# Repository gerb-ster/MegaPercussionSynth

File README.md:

# Mega Percussion Synth

A eurorack adaptation of Thomas Henry's MegaPercussionSynth

## Status: Work in Progress

- done: first schematic & board design
- todo: breadboard and test
- todo: design frontpanel
- todo: order PCB and build prototype

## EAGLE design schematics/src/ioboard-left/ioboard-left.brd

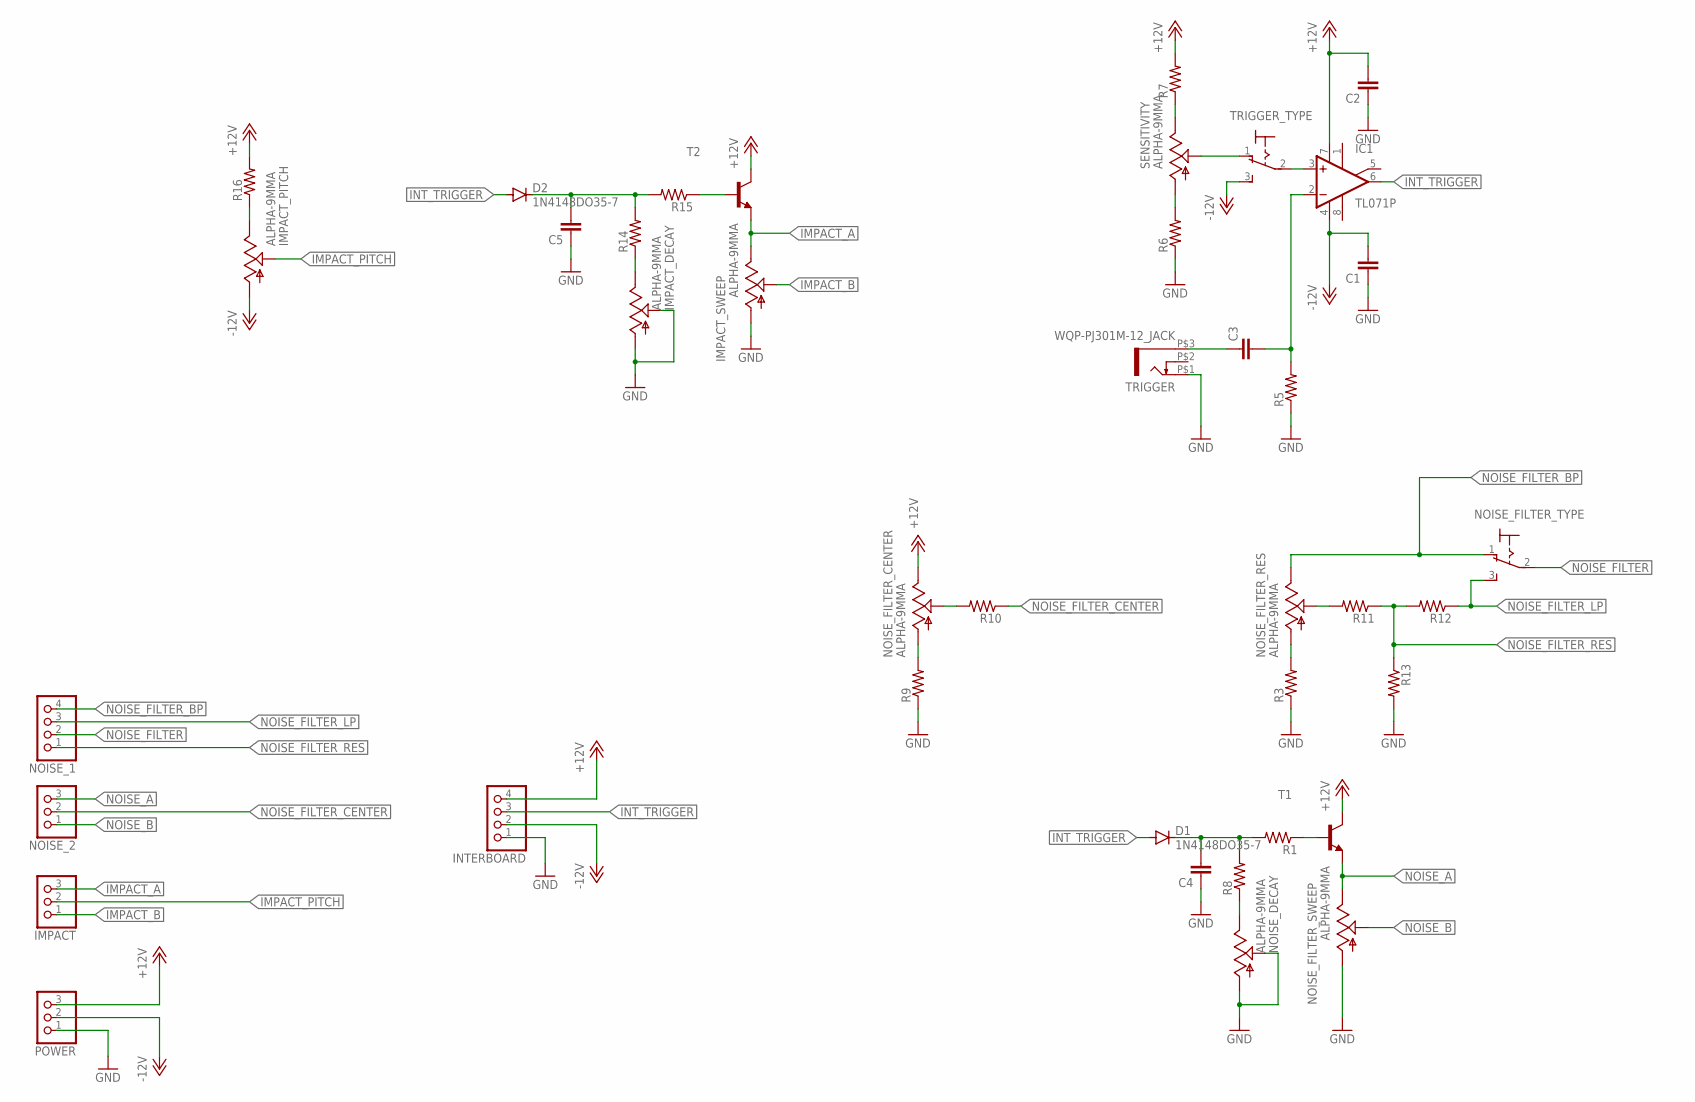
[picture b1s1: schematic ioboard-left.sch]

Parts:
C1, C2, C3, C4, C5: C-EU050-024X044; C050-024X044
D1, D2: 1N4148DO35-7; DO35-7
IC1: TL071P; DIL08
IMPACT: PINHD-1X3; 1X03
IMPACT_DECAY: ALPHA-9MMA; EVUF
IMPACT_PITCH: ALPHA-9MMA; EVUF
IMPACT_SWEEP: ALPHA-9MMA; EVUF
INTERBOARD: PINHD-1X4; 1X04
NOISE_1: PINHD-1X4; 1X04
NOISE_2: PINHD-1X3; 1X03
NOISE_DECAY: ALPHA-9MMA; EVUF
NOISE_FILTER_CENTER: ALPHA-9MMA; EVUF
NOISE_FILTER_RES: ALPHA-9MMA; EVUF
NOISE_FILTER_SWEEP: ALPHA-9MMA; EVUF
NOISE_FILTER_TYPE: M9040P
POWER: PINHD-1X3; 1X03
R1, R3, R5, R6, R7, R8, R9, R10, R11, R12, R13, R14, R15, R16: R-US_0207/7; 0207/7
SENSITIVITY: ALPHA-9MMA; EVUF
T1, T2: 2N3904-NPN-TO92-EBC; TO92-EBC
TRIGGER: WQP-PJ301M-12_JACK
TRIGGER_TYPE: M9040P

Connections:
+12V: C2.2, IC1.7 (V+), INTERBOARD.4, NOISE_FILTER_CENTER.3 (E), POWER.3, R7.2, R16.2, T1.C, T2.C
-12V: C1.2, IC1.4 (V-), IMPACT_PITCH.1 (A), INTERBOARD.2, POWER.2, TRIGGER_TYPE.3 (S)
GND: C1.1, C2.1, C4.1, C5.1, IMPACT_DECAY.1 (A), IMPACT_DECAY.2 (S), IMPACT_SWEEP.1 (A), INTERBOARD.1, NOISE_DECAY.1 (A), NOISE_DECAY.2 (S), NOISE_FILTER_SWEEP.1 (A), POWER.1, R3.1, R5.1, R6.1, R9.1, R13.2, TRIGGER.P$1 (2)
IMPACT_A: IMPACT.3, IMPACT_SWEEP.3 (E), T2.E
IMPACT_B: IMPACT.1, IMPACT_SWEEP.2 (S)
IMPACT_PITCH: IMPACT.2, IMPACT_PITCH.2 (S)
INT_TRIGGER: D1.A, D2.A, IC1.6 (OUT), INTERBOARD.3
unnamed: R7.1, SENSITIVITY.3 (E)
unnamed: R6.2, SENSITIVITY.1 (A)
unnamed: SENSITIVITY.2 (S), TRIGGER_TYPE.1 (O)
unnamed: IC1.3 (+IN), TRIGGER_TYPE.2
unnamed: C3.1, TRIGGER.P$3 (1)
unnamed: C3.2, IC1.2 (-IN), R5.2
unnamed: C4.2, D1.C, R1.2, R8.2
unnamed: NOISE_DECAY.3 (E), R8.1
unnamed: R1.1, T1.B
unnamed: NOISE_FILTER_CENTER.1 (A), R9.2
unnamed: NOISE_FILTER_CENTER.2 (S), R10.2
unnamed: NOISE_FILTER_RES.1 (A), R3.2
unnamed: NOISE_FILTER_RES.2 (S), R11.2
unnamed: C5.2, D2.C, R14.2, R15.2
unnamed: IMPACT_DECAY.3 (E), R14.1
unnamed: R15.1, T2.B
unnamed: IMPACT_PITCH.3 (E), R16.1
NOISE_A: NOISE_2.3, NOISE_FILTER_SWEEP.3 (E), T1.E
NOISE_B: NOISE_2.1, NOISE_FILTER_SWEEP.2 (S)
NOISE_FILTER: NOISE_1.2, NOISE_FILTER_TYPE.2
NOISE_FILTER_BP: NOISE_1.4, NOISE_FILTER_RES.3 (E), NOISE_FILTER_TYPE.1 (O)
NOISE_FILTER_CENTER: NOISE_2.2, R10.1
NOISE_FILTER_LP: NOISE_1.3, NOISE_FILTER_TYPE.3 (S), R12.1
NOISE_FILTER_RES: NOISE_1.1, R11.1, R12.2, R13.1

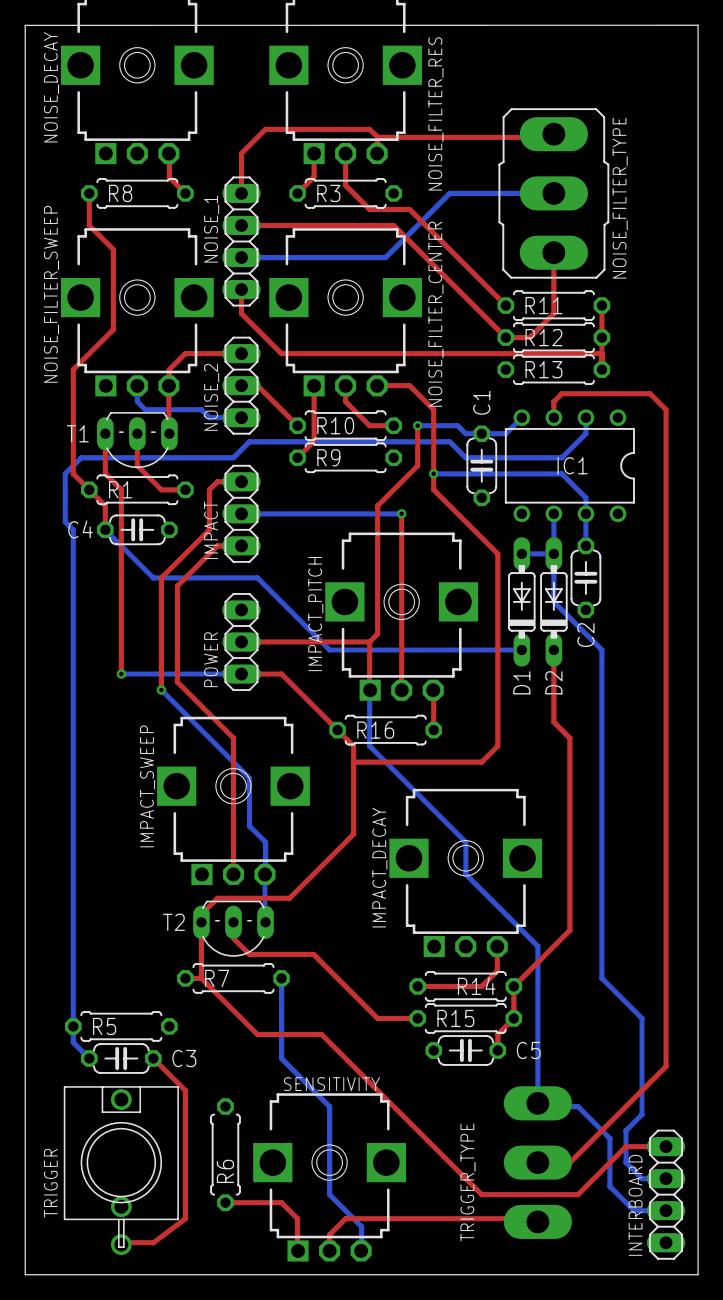
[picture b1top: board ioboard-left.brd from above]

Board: 2 copper layers, 53.3 x 99.1 mm, 40 parts (1 on the bottom side), 31 nets.

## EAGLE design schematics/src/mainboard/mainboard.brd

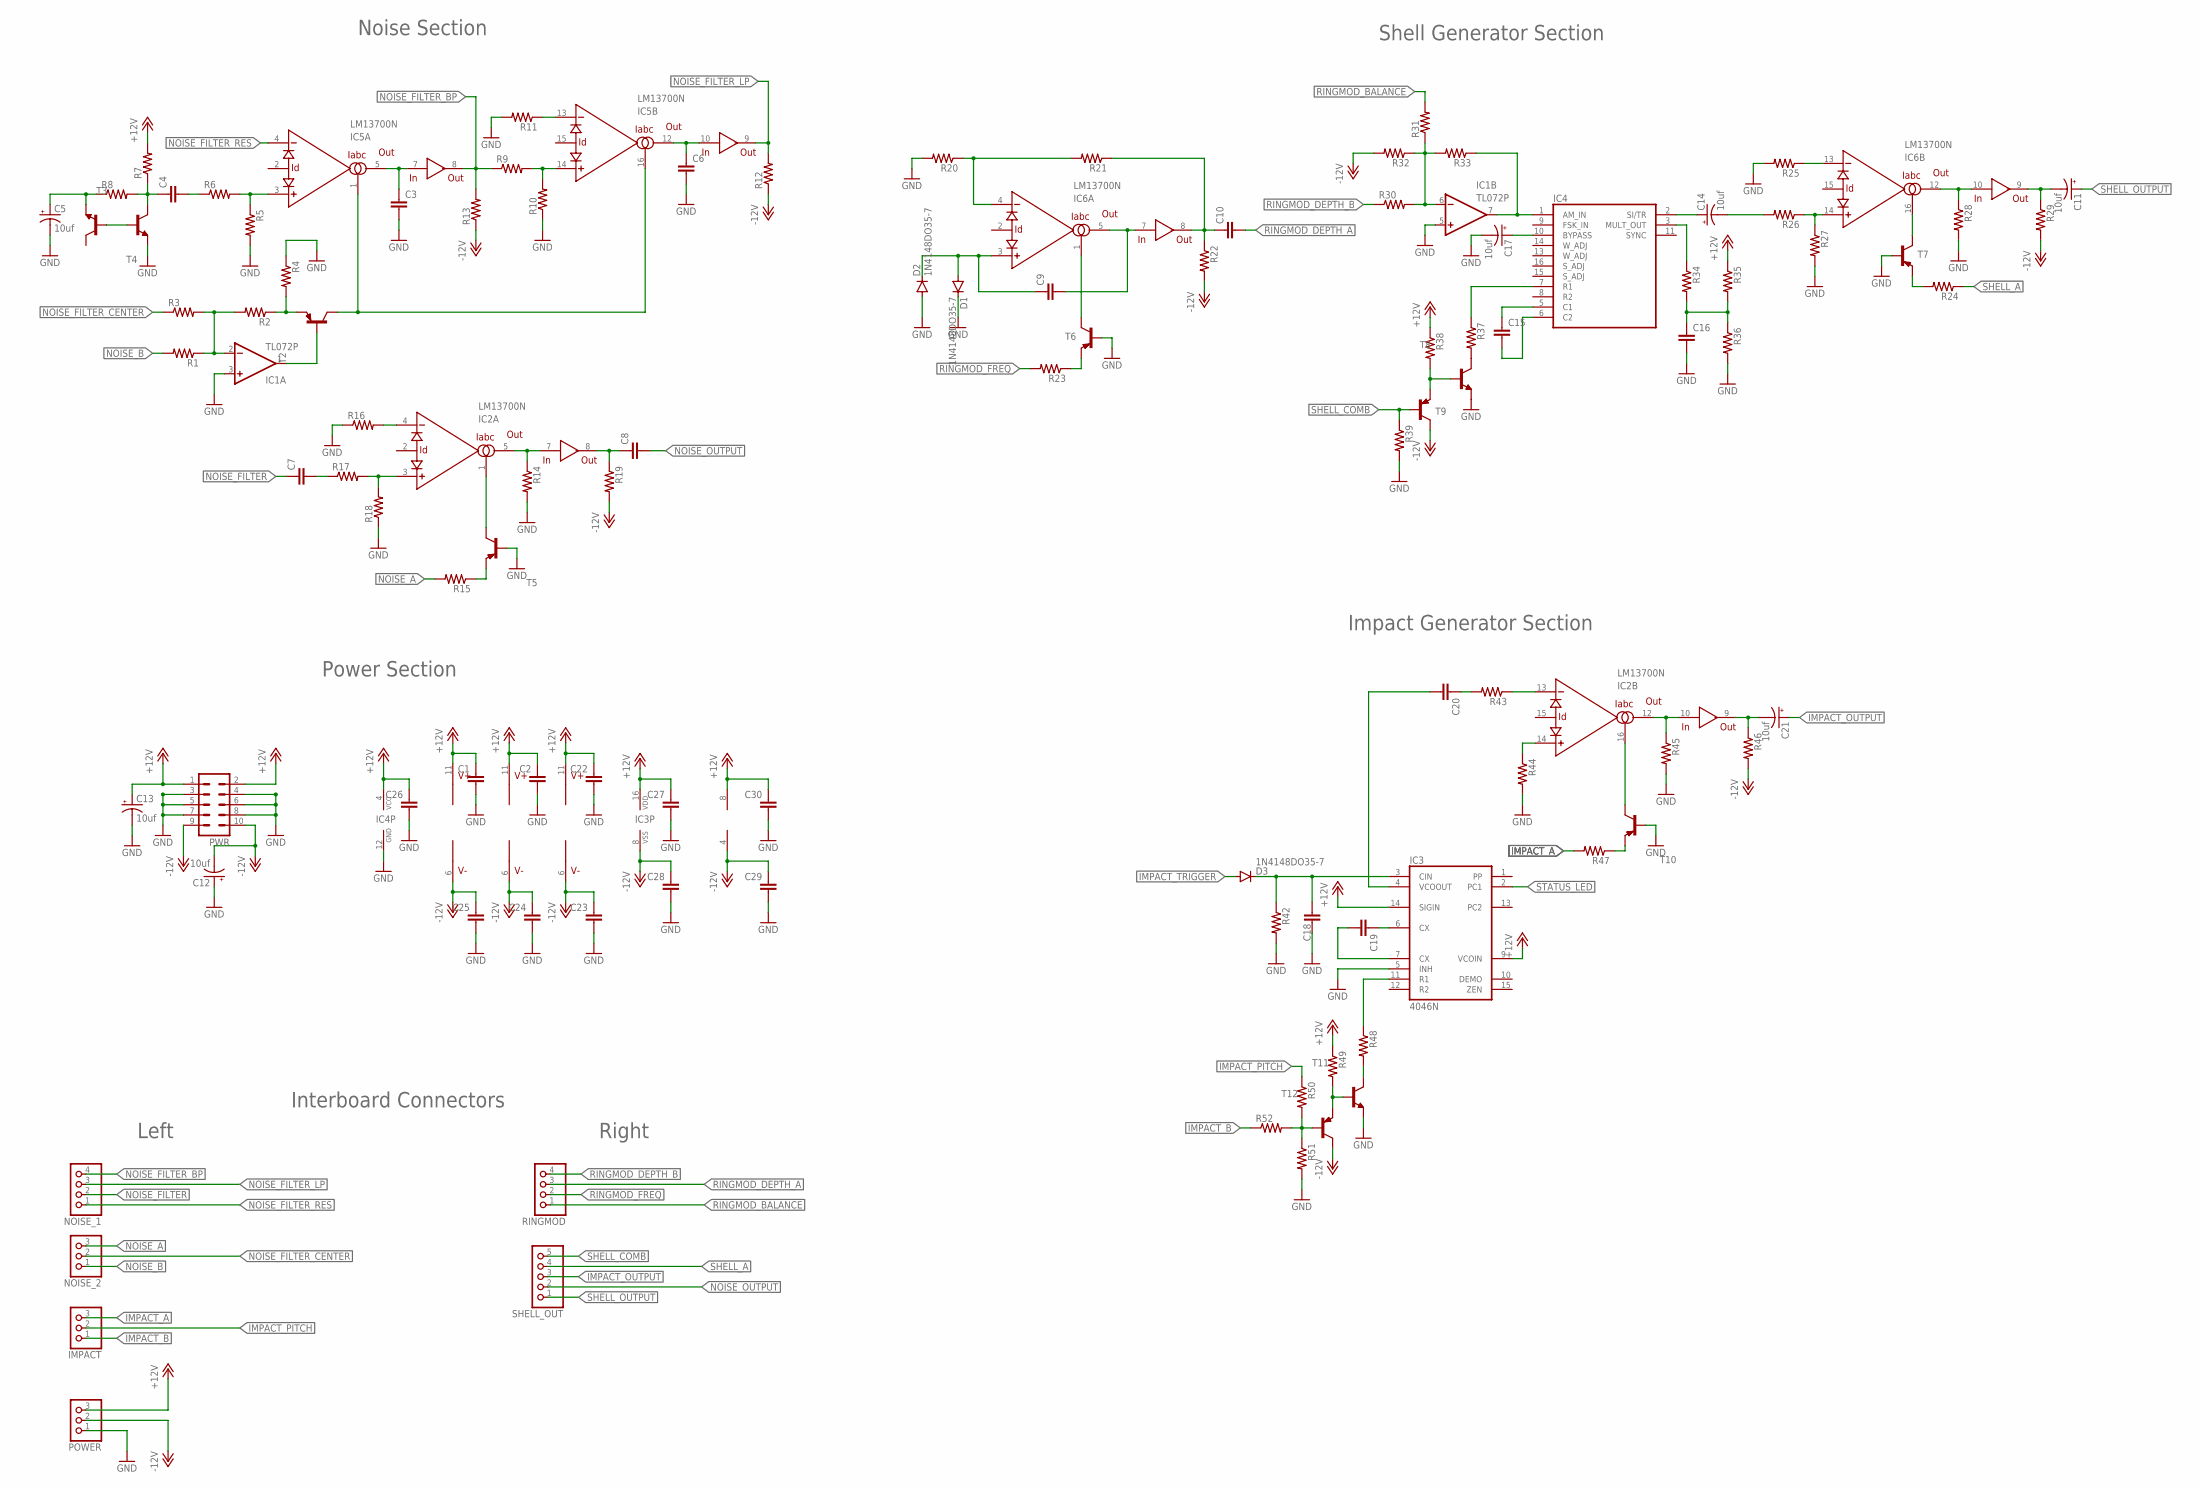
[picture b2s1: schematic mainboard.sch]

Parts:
C1, C2, C3, C4, C6, C7, C8, C9, C10, C15, C16, C18, C19, C20, C22, C23, C24, C25, C26, C27, C28, C29, C30: C-EU050-024X044; C050-024X044
C5, C11, C12, C13, C14, C17, C21: 10uf; E2,5-5
D1, D2, D3: 1N4148DO35-7; DO35-7
IC1: TL072P; DIL08
IC2, IC5, IC6: LM13700N; DIL16
IC3: 4046N; DIL16
IC4: XR-2206; DIL16
IMPACT: PINHD-1X3; 1X03
NOISE_1: PINHD-1X4; 1X04
NOISE_2: PINHD-1X3; 1X03
POWER: PINHD-1X3; 1X03
PWR: ML10
R1, R2, R3, R4, R5, R6, R7, R8, R9, R10, R11, R12, R13, R14, R15, R16, R17, R18, R19, R20, R21, R22, R23, R24, R25, R26, R27, R28, R29, R30, R31, R32, R33, R34, R35, R36, R37, R38, R39, R42, R43, R44, R45, R46, R47, R48, R49, R50, R51, R52: R-US_0207/7; 0207/7
RINGMOD: PINHD-1X4; 1X04
SHELL_OUT: PINHD-1X5; 1X05
T2, T5, T6, T7, T9, T10, T12: 2N3906-PNP-TO92-EBC; TO92-EBC
T3, T4, T8, T11: 2N3904-NPN-TO92-EBC; TO92-EBC

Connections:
+12V: C1.1, C2.1, C13.+, C22.1, C26.1, C27.1, C30.1, IC1.8 (V+), IC2.11 (V+), IC3.9 (VCOIN), IC3.14 (SIGIN), IC3.16 (VDD), IC4.4 (VCC), IC5.11 (V+), IC6.11 (V+), POWER.3, PWR.1, PWR.2, R7.2, R35.1, R38.1, R49.1
-12V: C12.-, C23.1, C24.1, C25.1, C28.1, C29.1, IC1.4 (V-), IC2.6 (V-), IC3.8 (VSS), IC5.6 (V-), IC6.6 (V-), POWER.2, PWR.9, PWR.10, R12.1, R13.1, R19.2, R22.2, R29.2, R32.2, R46.2, T9.C, T12.C
GND: C1.2, C2.2, C3.2, C5.-, C6.2, C12.+, C13.-, C16.2, C17.-, C18.1, C22.2, C23.2, C24.2, C25.2, C26.2, C27.2, C28.2, C29.2, C30.2, D1.C, D2.A, IC1.3 (+IN), IC1.5 (+IN), IC3.5 (INH), IC4.12 (GND), POWER.1, PWR.3, PWR.4, PWR.5, PWR.6, PWR.7, PWR.8, R4.1, R5.2, R10.1, R11.2, R14.2, R16.1, R18.1, R20.2, R25.2, R27.2, R28.2, R36.2, R39.2, R42.2, R44.2, R45.2, R51.2, T3.E, T5.B, T6.B, T7.B, T8.E, T10.B, T11.E
IMPACT_A: IMPACT.3, R47.2
IMPACT_B: IMPACT.1, R52.1
IMPACT_OUTPUT: C21.+, SHELL_OUT.3
IMPACT_PITCH: IMPACT.2, R50.1
IMPACT_TRIGGER: D3.A
unnamed: IC1.2 (-IN), R1.1, R2.2, R3.2
unnamed: IC5.1 (IABC), IC5.16 (IABC), T2.C
unnamed: IC1.1 (OUT), T2.B
unnamed: R2.1, R4.2, T2.E
unnamed: C3.1, IC5.5 (OUT), IC5.7 (IN)
unnamed: C5.+, R8.1, T4.E
unnamed: C4.1, R7.1, R8.2, T3.C
unnamed: T3.B, T4.B
unnamed: C4.2, R6.1
unnamed: IC5.3 (+IN), R5.1, R6.2
unnamed: C6.1, IC5.10 (IN), IC5.12 (OUT)
unnamed: IC5.14 (+IN), R9.2, R10.2
unnamed: IC5.13 (-IN), R11.1
unnamed: IC2.4 (-IN), R16.2
unnamed: IC2.3 (+IN), R17.2, R18.2
unnamed: C7.2, R17.1
unnamed: IC2.1 (IABC), T5.C
unnamed: C9.1, D1.A, D2.C, IC6.3 (+IN)
unnamed: R15.1, T5.E
unnamed: IC2.5 (OUT), IC2.7 (IN), R14.1
unnamed: C8.1, IC2.8 (OUT), R19.1
unnamed: C9.2, IC6.5 (OUT), IC6.7 (IN)
unnamed: C10.1, IC6.8 (OUT), R21.1, R22.1
unnamed: IC6.1 (IABC), T6.C
unnamed: R23.1, T6.E
unnamed: IC6.4 (-IN), R20.1, R21.2
unnamed: IC1.6 (-IN), R30.2, R31.1, R32.1, R33.2
unnamed: IC1.7 (OUT), IC4.1 (AM_IN), R33.1
unnamed: C14.+, IC4.2 (SI/TR)
unnamed: C14.-, R26.2
unnamed: IC6.14 (+IN), R26.1, R27.1
unnamed: IC6.13 (-IN), R25.1
unnamed: IC6.16 (IABC), T7.C
unnamed: IC6.10 (IN), IC6.12 (OUT), R28.1
unnamed: R24.2, T7.E
unnamed: C11.-, IC6.9 (OUT), R29.1
unnamed: C15.2, IC4.6 (C2)
unnamed: C15.1, IC4.5 (C1)
unnamed: IC4.3 (MULT_OUT), R34.1
unnamed: C17.+, IC4.10 (BYPASS)
unnamed: C16.1, R34.2, R35.2, R36.1
unnamed: IC4.7 (R1), R37.1
unnamed: R37.2, T8.C
unnamed: R38.2, T8.B, T9.E
unnamed: C20.1, R43.2
unnamed: IC2.13 (-IN), R43.1
unnamed: IC2.14 (+IN), R44.1
unnamed: IC2.10 (IN), IC2.12 (OUT), R45.1
unnamed: IC2.16 (IABC), T10.C
unnamed: R50.2, R51.1, R52.2, T12.B
unnamed: R47.1, T10.E
unnamed: C21.-, IC2.9 (OUT), R46.1
unnamed: C20.2, IC3.4 (VCOOUT)
unnamed: C19.1, IC3.6 (CX)
unnamed: C19.2, IC3.7 (CX)
unnamed: R49.2, T11.B, T12.E
unnamed: C18.2, D3.C, IC3.3 (CIN), R42.1
unnamed: R48.2, T11.C
unnamed: IC3.11 (R1), R48.1
NOISE_A: NOISE_2.3, R15.2
NOISE_B: NOISE_2.1, R1.2
NOISE_FILTER: C7.1, NOISE_1.2
NOISE_FILTER_BP: IC5.8 (OUT), NOISE_1.4, R9.1, R13.2
NOISE_FILTER_CENTER: NOISE_2.2, R3.1
NOISE_FILTER_LP: IC5.9 (OUT), NOISE_1.3, R12.2
NOISE_FILTER_RES: IC5.4 (-IN), NOISE_1.1
NOISE_OUTPUT: C8.2, SHELL_OUT.2
RINGMOD_BALANCE: R31.2, RINGMOD.1
RINGMOD_DEPTH_A: C10.2, RINGMOD.3
RINGMOD_DEPTH_B: R30.1, RINGMOD.4
RINGMOD_FREQ: R23.2, RINGMOD.2
SHELL_A: R24.1, SHELL_OUT.4
SHELL_COMB: R39.1, SHELL_OUT.5, T9.B
SHELL_OUTPUT: C11.+, SHELL_OUT.1
STATUS_LED: IC3.2 (PC1)

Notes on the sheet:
Noise Section
Shell Generator Section
Impact Generator Section
Power Section
Interboard Connectors
Left
Right

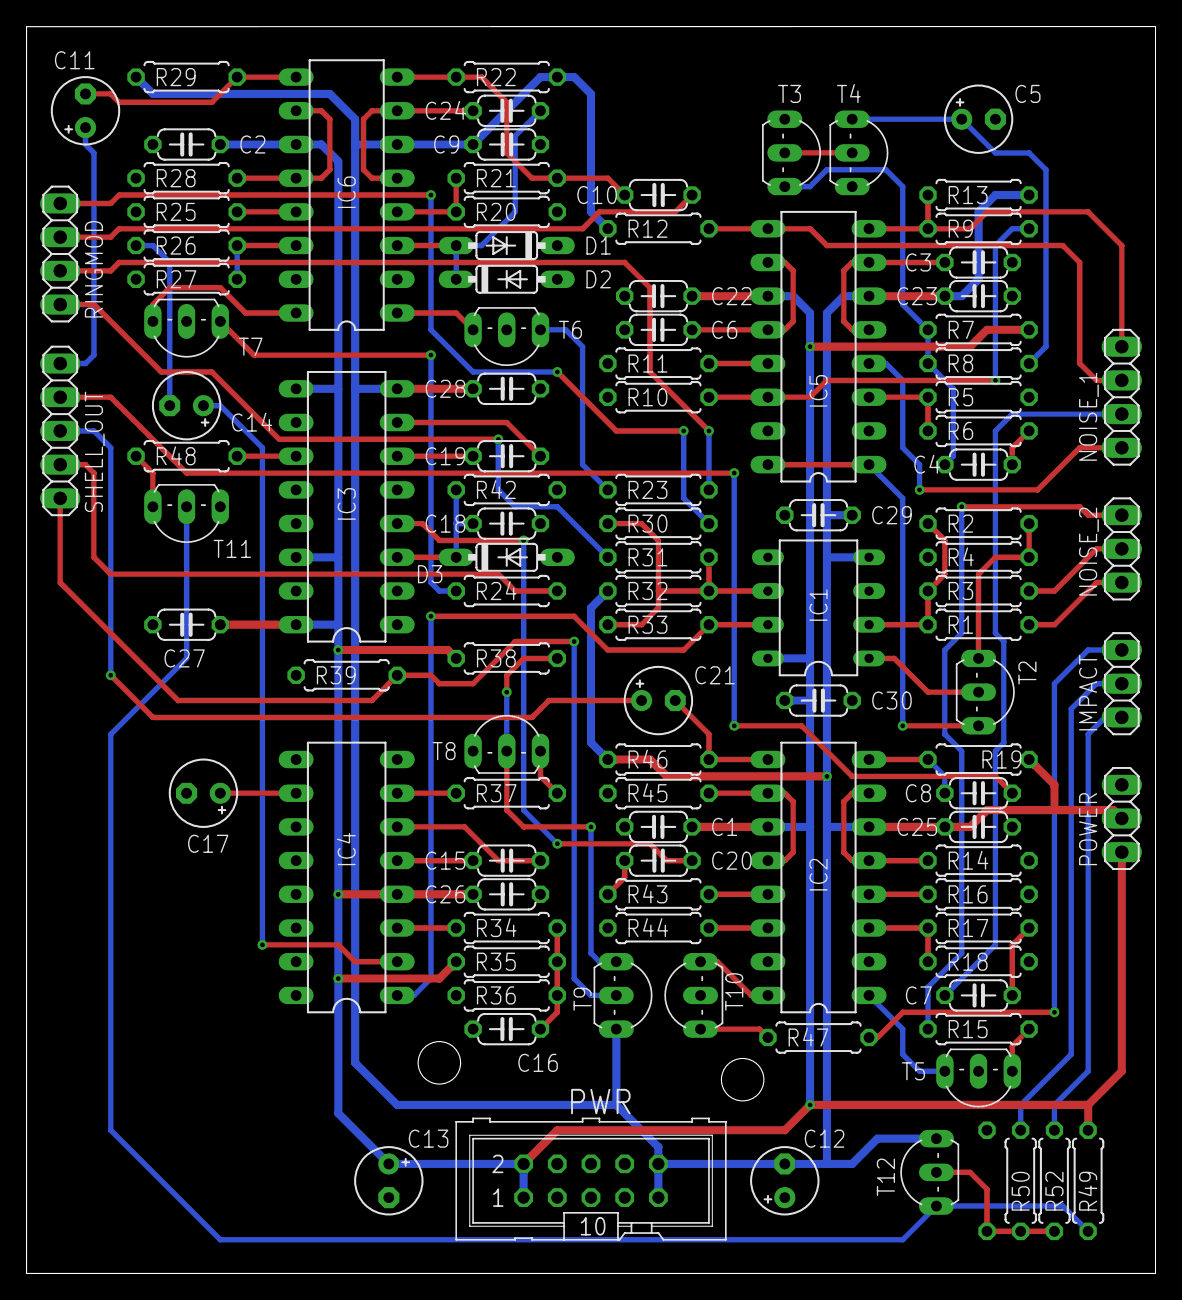
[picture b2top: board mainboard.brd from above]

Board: 2 copper layers, 85.1 x 94.0 mm, 107 parts (1 on the bottom side), 81 nets.

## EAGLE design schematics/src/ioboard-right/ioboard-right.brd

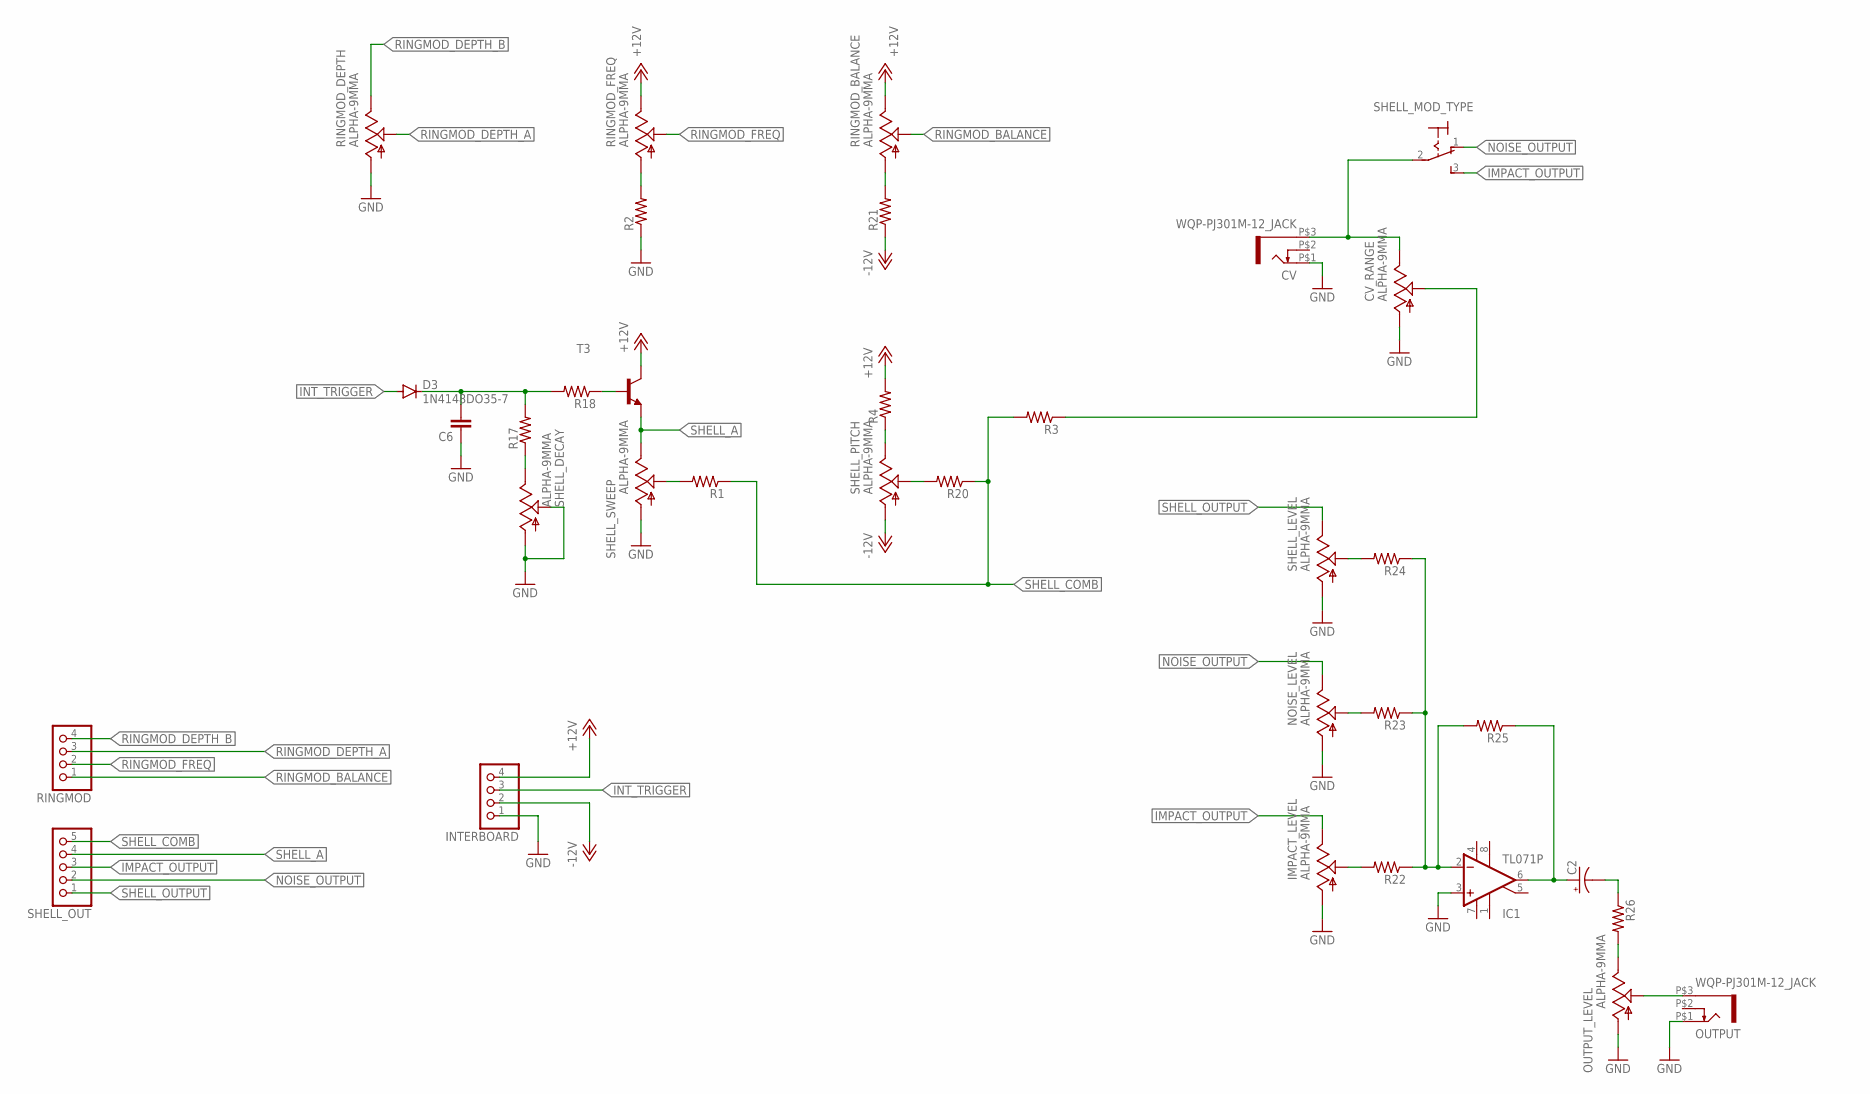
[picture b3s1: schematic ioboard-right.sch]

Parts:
C2: CPOL-USE2.5-6; E2,5-6
C6: C-EU050-024X044; C050-024X044
CV: WQP-PJ301M-12_JACK
CV_RANGE: ALPHA-9MMA; EVUF
D3: 1N4148DO35-7; DO35-7
IC1: TL071P; DIL08
IMPACT_LEVEL: ALPHA-9MMA; EVUF
INTERBOARD: PINHD-1X4; 1X04
NOISE_LEVEL: ALPHA-9MMA; EVUF
OUTPUT: WQP-PJ301M-12_JACK
OUTPUT_LEVEL: ALPHA-9MMA; EVUF
R1, R2, R3, R4, R17, R18, R20, R21, R22, R23, R24, R25, R26: R-US_0207/7; 0207/7
RINGMOD: PINHD-1X4; 1X04
RINGMOD_BALANCE: ALPHA-9MMA; EVUF
RINGMOD_DEPTH: ALPHA-9MMA; EVUF
RINGMOD_FREQ: ALPHA-9MMA; EVUF
SHELL_DECAY: ALPHA-9MMA; EVUF
SHELL_LEVEL: ALPHA-9MMA; EVUF
SHELL_MOD_TYPE: M9040P
SHELL_OUT: PINHD-1X5; 1X05
SHELL_PITCH: ALPHA-9MMA; EVUF
SHELL_SWEEP: ALPHA-9MMA; EVUF
T3: 2N3904-NPN-TO92-EBC; TO92-EBC

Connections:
+12V: INTERBOARD.4, R4.2, RINGMOD_BALANCE.3 (E), RINGMOD_FREQ.3 (E), T3.C
-12V: INTERBOARD.2, R21.1, SHELL_PITCH.1 (A)
GND: C6.1, CV.P$1 (2), CV_RANGE.1 (A), IC1.3 (+IN), IMPACT_LEVEL.1 (A), INTERBOARD.1, NOISE_LEVEL.1 (A), OUTPUT.P$1 (2), OUTPUT_LEVEL.1 (A), R2.1, RINGMOD_DEPTH.1 (A), SHELL_DECAY.1 (A), SHELL_DECAY.2 (S), SHELL_LEVEL.1 (A), SHELL_SWEEP.1 (A)
IMPACT_OUTPUT: IMPACT_LEVEL.3 (E), SHELL_MOD_TYPE.3 (S), SHELL_OUT.3
INT_TRIGGER: D3.A, INTERBOARD.3
unnamed: R1.2, SHELL_SWEEP.2 (S)
unnamed: CV_RANGE.2 (S), R3.1
unnamed: C6.2, D3.C, R17.2, R18.2
unnamed: R18.1, T3.B
unnamed: R17.1, SHELL_DECAY.3 (E)
unnamed: R2.2, RINGMOD_FREQ.1 (A)
unnamed: R21.2, RINGMOD_BALANCE.1 (A)
unnamed: R4.1, SHELL_PITCH.3 (E)
unnamed: R20.2, SHELL_PITCH.2 (S)
unnamed: CV.P$3 (1), CV_RANGE.3 (E), SHELL_MOD_TYPE.2
unnamed: IMPACT_LEVEL.2 (S), R22.2
unnamed: NOISE_LEVEL.2 (S), R23.2
unnamed: R24.2, SHELL_LEVEL.2 (S)
unnamed: IC1.2 (-IN), R22.1, R23.1, R24.1, R25.2
unnamed: OUTPUT_LEVEL.3 (E), R26.2
unnamed: OUTPUT.P$3 (1), OUTPUT_LEVEL.2 (S)
unnamed: C2.+, IC1.6 (OUT), R25.1
unnamed: C2.-, R26.1
NOISE_OUTPUT: NOISE_LEVEL.3 (E), SHELL_MOD_TYPE.1 (O), SHELL_OUT.2
RINGMOD_BALANCE: RINGMOD.1, RINGMOD_BALANCE.2 (S)
RINGMOD_DEPTH_A: RINGMOD.3, RINGMOD_DEPTH.2 (S)
RINGMOD_DEPTH_B: RINGMOD.4, RINGMOD_DEPTH.3 (E)
RINGMOD_FREQ: RINGMOD.2, RINGMOD_FREQ.2 (S)
SHELL_A: SHELL_OUT.4, SHELL_SWEEP.3 (E), T3.E
SHELL_COMB: R1.1, R3.2, R20.1, SHELL_OUT.5
SHELL_OUTPUT: SHELL_LEVEL.3 (E), SHELL_OUT.1
V+: IC1.7 (V+)
V-: IC1.4 (V-)

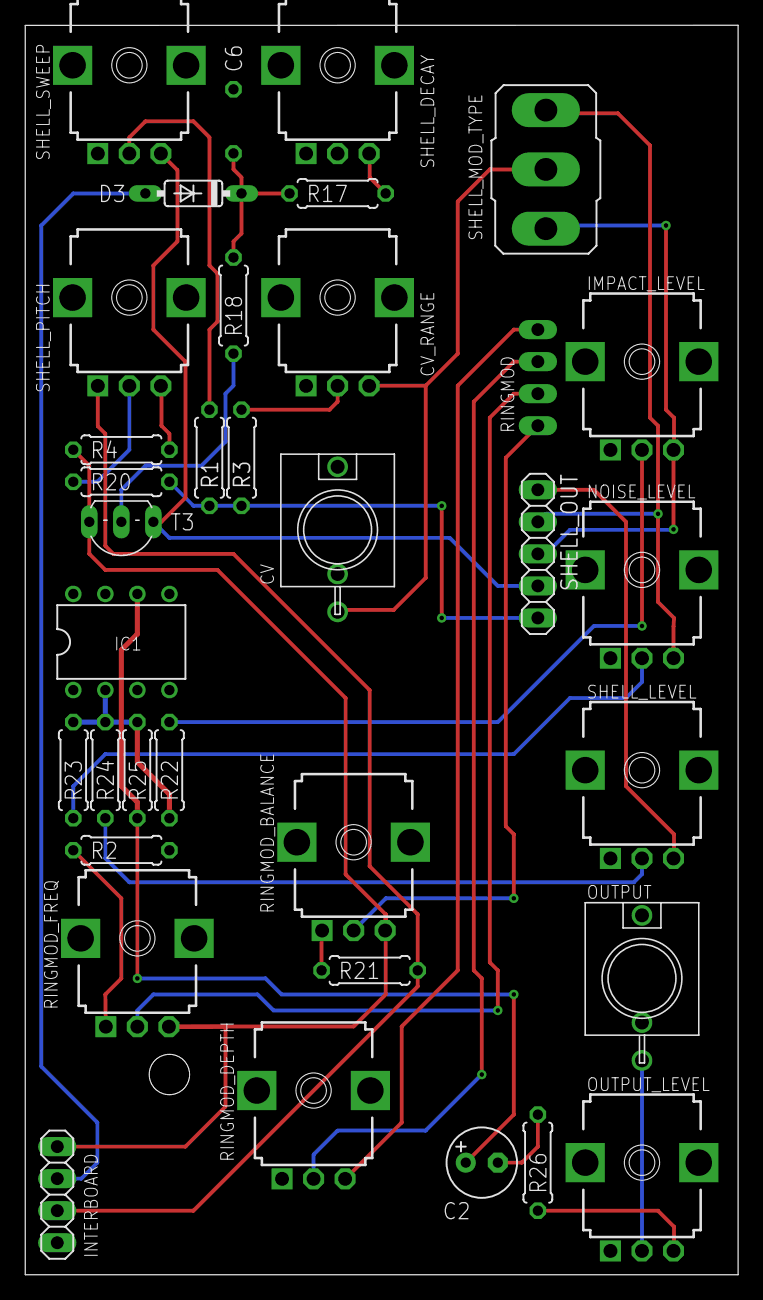
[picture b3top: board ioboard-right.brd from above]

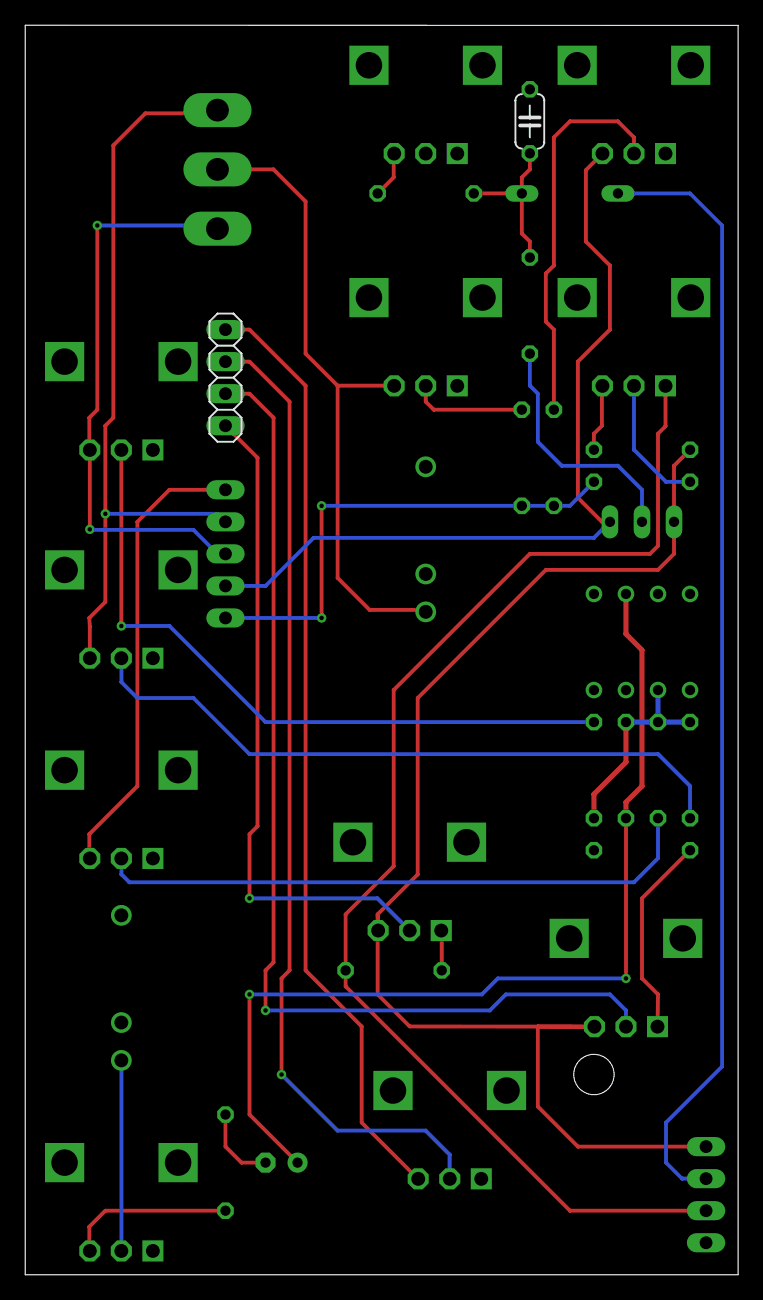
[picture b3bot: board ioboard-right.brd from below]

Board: 2 copper layers, 56.5 x 99.1 mm, 35 parts (2 on the bottom side), 31 nets.

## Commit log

2021-05-07 Added files & structure
2021-05-10 Added Status
2021-05-11 Added Status & Images
2021-08-06 Updated some schematics and docs
2021-08-10 Fixed some bugs and updated documentation
2022-04-20 Some updates & bugfixes
2022-04-22 Fixed schematics & descriptions
2022-05-17 Updated Firmware
2022-05-18 Updated Faceplates
2022-05-18 Fixed issues
2022-05-21 Fixed schematics
2022-05-28 General updates
